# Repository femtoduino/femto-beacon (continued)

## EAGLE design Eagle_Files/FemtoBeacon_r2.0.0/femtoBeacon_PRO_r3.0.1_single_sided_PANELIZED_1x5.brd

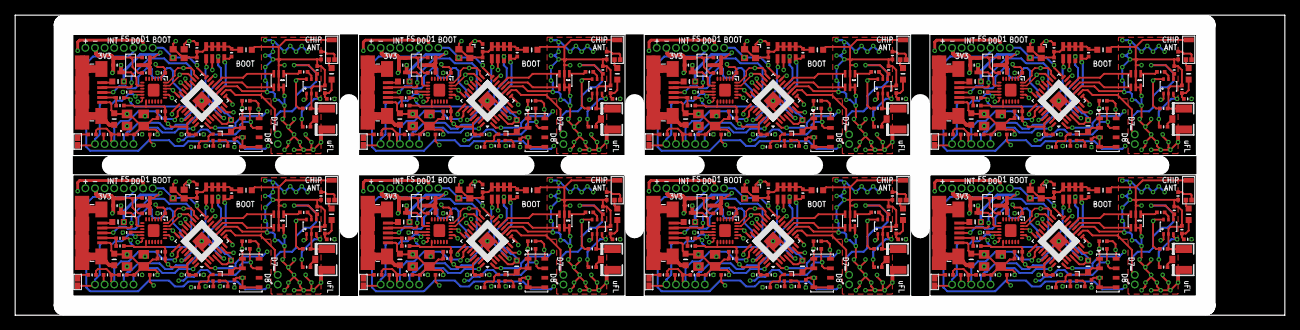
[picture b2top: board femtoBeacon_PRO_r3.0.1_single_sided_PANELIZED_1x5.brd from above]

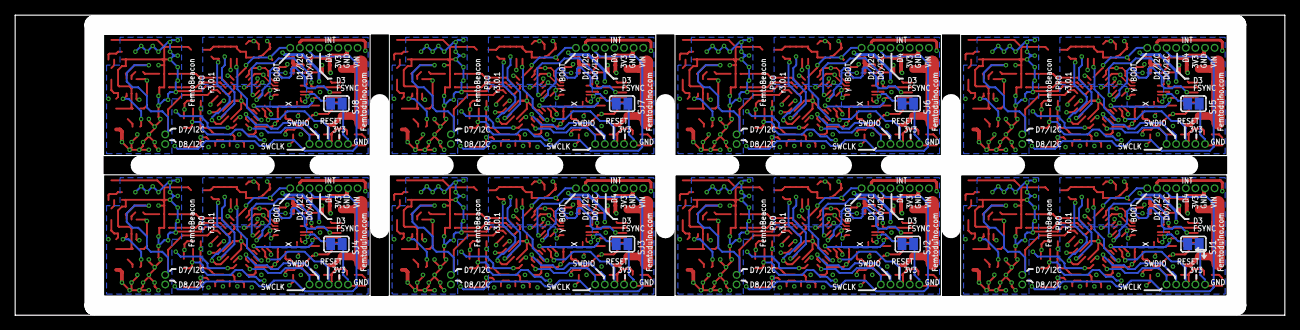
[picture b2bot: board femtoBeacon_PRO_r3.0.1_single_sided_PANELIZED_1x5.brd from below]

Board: 4 copper layers, 167.6 x 39.6 mm, 440 parts (8 on the bottom side), 352 nets.

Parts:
ASWITCH, ASWITCH1, ASWITCH2, ASWITCH3, ASWITCH4, ASWITCH5, ASWITCH6, ASWITCH7: AS222-92LF
BALUN, BALUN1, BALUN2, BALUN3, BALUN4, BALUN5, BALUN6, BALUN7: JOHANSON_2450BM15A0015E; 0805_BALUN
BARO, BARO1, BARO2, BARO3, BARO4, BARO5, BARO6, BARO7: MS5611-01BA03
BTN_RESET, BTN_RESET1, BTN_RESET2, BTN_RESET3, BTN_RESET4, BTN_RESET5, BTN_RESET6, BTN_RESET7: DNP; SPST_SMD
C1, C10, C16, C18, C24, C25, C28, C29, C30, C32, C39, C40, C47, C51, C52, C55, C62, C63, C70, C74, C75, C78, C85, C86, C93, C97, C98, C101, C108, C109, C116, C120, C121, C124, C131, C132, C139, C143, C144, C147, C154, C155, C162, C166, C167, C170, C177, C178: 0.1uF; _0402MP
C2, C8, C9, C11, C12, C41, C42, C43, C44, C45, C64, C65, C66, C67, C68, C87, C88, C89, C90, C91, C110, C111, C112, C113, C114, C133, C134, C135, C136, C137, C156, C157, C158, C159, C160, C179, C180, C181, C182, C183: 22pF, C0G, 5%; _0402MP
C3, C4, C33, C34, C56, C57, C79, C80, C102, C103, C125, C126, C148, C149, C171, C172: 10pF; _0402MP
C5, C6, C19, C20, C48, C49, C71, C72, C94, C95, C117, C118, C140, C141, C163, C164: 2.2uF; _0402MP
C7, C23, C50, C73, C96, C119, C142, C165: 0.47uF; _0402MP
C13, C35, C58, C81, C104, C127, C150, C173: DNP; _0402MP
C14, C15, C36, C37, C59, C60, C82, C83, C105, C106, C128, C129, C151, C152, C174, C175: 9pF; _0402MP
C17, C46, C69, C92, C115, C138, C161, C184: 1.2pF; _0402MP
C21, C22, C26, C27, C53, C54, C76, C77, C99, C100, C122, C123, C145, C146, C168, C169: 10uF; _0402MP
C31, C38, C61, C84, C107, C130, C153, C176: 10000pF; _0402MP
C_ARR, C_ARR1, C_ARR2, C_ARR3, C_ARR4, C_ARR5, C_ARR6, C_ARR7: 0.1uF; CAPACITOR_ARRAY_1206_MONO_1X4
FB1, FB2, FB3, FB4, FB5, FB6, FB7, FB8, FB9, FB10, FB11, FB12, FB13, FB14, FB15, FB16, FB17, FB18, FB19, FB20, FB21, FB22, FB23, FB24: _0603MP
IC, IC1, IC2, IC3, IC4, IC5, IC6, IC7: ATSAMR21E18A-MUT; QFN32
IMU, IMU1, IMU2, IMU3, IMU4, IMU5, IMU6, IMU7: MPU-9250; QFN_3X3MM
L1, L3, L5, L8, L10, L12, L14, L16: 1.8nH; _0603MP
L2, L4, L6, L7, L9, L11, L13, L15: 10uH; _0603MP
LDO_VREG, LDO_VREG1, LDO_VREG2, LDO_VREG3, LDO_VREG4, LDO_VREG5, LDO_VREG6, LDO_VREG7: MCP1700T-3302E/TT
R1, R3, R4, R6, R7, R10, R12, R15, R17, R18, R19, R21, R24, R26, R27, R28, R30, R33, R35, R36, R37, R39, R42, R44, R45, R46, R48, R51, R53, R54, R55, R57, R60, R62, R63, R64, R66, R69, R71, R72: 330; _0402MP
R2, R11, R20, R29, R38, R47, R56, R65: 10K; _0402MP
R5, R16, R25, R34, R43, R52, R61, R70: 100K; _0402MP
R8, R9, R13, R14, R22, R23, R31, R32, R40, R41, R49, R50, R58, R59, R67, R68: 2.2K; _0402MP
RGBLED, RGBLED1, RGBLED2, RGBLED3, RGBLED4, RGBLED5, RGBLED6, RGBLED7: LRTB_R48G
SJ1, SJ2, SJ3, SJ4, SJ5, SJ6, SJ7, SJ8: SOLDERJUMPER_CLOSEDWIRE
SMDANT, SMDANT1, SMDANT2, SMDANT3, SMDANT4, SMDANT5, SMDANT6, SMDANT7: PULSE_ANT_2.4GHZ; ANT_BAR
U$1, U$4, U$5, U$8, U$13, U$16, U$19, U$22: 1X8_ROUND
U$2, U$6, U$10, U$11, U$14, U$17, U$20, U$23: 1X5_ROUND
U$3, U$7, U$9, U$12, U$15, U$18, U$21, U$24: 1X2_ROUND
UFLANT, UFLANT1, UFLANT2, UFLANT3, UFLANT4, UFLANT5, UFLANT6, UFLANT7: U.FL
USB, USB1, USB2, USB3, USB4, USB5, USB6, USB7: USB_MICROB; USB_MICROB_PACKAGE
XTAL_BOARD, XTAL_BOARD1, XTAL_BOARD2, XTAL_BOARD3, XTAL_BOARD4, XTAL_BOARD5, XTAL_BOARD6, XTAL_BOARD7: 32MHz; FA-128
XTAL_RF, XTAL_RF1, XTAL_RF2, XTAL_RF3, XTAL_RF4, XTAL_RF5, XTAL_RF6, XTAL_RF7: 16MHz; TSX-3225

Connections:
3.3V: BARO.1, BARO.2, C5.1, C10.1, C16.1, C21.2, C29.1, C30.2, C31.2, IC.24, IC.30, IMU.P$1, IMU.P$8, IMU.P$13, IMU.P$22, L6.1, LDO_VREG.VOUT, R2.1, R5.2, R8.2, R9.2, RGBLED.1, U$5.P$3, U$10.P$2
3.3V1: BARO1.1, BARO1.2, C19.1, C24.1, C25.1, C26.2, C28.1, C38.2, C39.2, IC1.24, IC1.30, IMU1.P$1, IMU1.P$8, IMU1.P$13, IMU1.P$22, L2.1, LDO_VREG1.VOUT, R11.1, R13.2, R14.2, R16.2, RGBLED1.1, U$1.P$3, U$2.P$2
3.3V2: BARO2.1, BARO2.2, C48.1, C51.1, C52.1, C53.2, C55.1, C61.2, C62.2, IC2.24, IC2.30, IMU2.P$1, IMU2.P$8, IMU2.P$13, IMU2.P$22, L4.1, LDO_VREG2.VOUT, R20.1, R22.2, R23.2, R25.2, RGBLED2.1, U$4.P$3, U$6.P$2
3.3V3: BARO3.1, BARO3.2, C71.1, C74.1, C75.1, C76.2, C78.1, C84.2, C85.2, IC3.24, IC3.30, IMU3.P$1, IMU3.P$8, IMU3.P$13, IMU3.P$22, L7.1, LDO_VREG3.VOUT, R29.1, R31.2, R32.2, R34.2, RGBLED3.1, U$8.P$3, U$11.P$2
3.3V4: BARO4.1, BARO4.2, C94.1, C97.1, C98.1, C99.2, C101.1, C107.2, C108.2, IC4.24, IC4.30, IMU4.P$1, IMU4.P$8, IMU4.P$13, IMU4.P$22, L9.1, LDO_VREG4.VOUT, R38.1, R40.2, R41.2, R43.2, RGBLED4.1, U$13.P$3, U$14.P$2
3.3V5: BARO5.1, BARO5.2, C117.1, C120.1, C121.1, C122.2, C124.1, C130.2, C131.2, IC5.24, IC5.30, IMU5.P$1, IMU5.P$8, IMU5.P$13, IMU5.P$22, L11.1, LDO_VREG5.VOUT, R47.1, R49.2, R50.2, R52.2, RGBLED5.1, U$16.P$3, U$17.P$2
3.3V6: BARO6.1, BARO6.2, C140.1, C143.1, C144.1, C145.2, C147.1, C153.2, C154.2, IC6.24, IC6.30, IMU6.P$1, IMU6.P$8, IMU6.P$13, IMU6.P$22, L13.1, LDO_VREG6.VOUT, R56.1, R58.2, R59.2, R61.2, RGBLED6.1, U$19.P$3, U$20.P$2
3.3V7: BARO7.1, BARO7.2, C163.1, C166.1, C167.1, C168.2, C170.1, C176.2, C177.2, IC7.24, IC7.30, IMU7.P$1, IMU7.P$8, IMU7.P$13, IMU7.P$22, L15.1, LDO_VREG7.VOUT, R65.1, R67.2, R68.2, R70.2, RGBLED7.1, U$22.P$3, U$23.P$2
ANT_OUT: BALUN.1, C2.1
ANT_OUT1: BALUN1.1, C41.1
ANT_OUT2: BALUN2.1, C64.1
ANT_OUT3: BALUN3.1, C87.1
ANT_OUT4: BALUN4.1, C110.1
ANT_OUT5: BALUN5.1, C133.1
ANT_OUT6: BALUN6.1, C156.1
ANT_OUT7: BALUN7.1, C179.1
ANT_SMD: C12.2, C17.1, L1.1
ANT_SMD1: C45.2, C46.1, L3.1
ANT_SMD2: C68.2, C69.1, L5.1
ANT_SMD3: C91.2, C92.1, L8.1
ANT_SMD4: C114.2, C115.1, L10.1
ANT_SMD5: C137.2, C138.1, L12.1
ANT_SMD6: C160.2, C161.1, L14.1
ANT_SMD7: C183.2, C184.1, L16.1
ANT_UFL: C11.2, UFLANT.3
ANT_UFL1: C44.2, UFLANT1.3
ANT_UFL2: C67.2, UFLANT2.3
ANT_UFL3: C90.2, UFLANT3.3
ANT_UFL4: C113.2, UFLANT4.3
ANT_UFL5: C136.2, UFLANT5.3
ANT_UFL6: C159.2, UFLANT6.3
ANT_UFL7: C182.2, UFLANT7.3
AVDD: C_ARR.3, IC.5
AVDD1: C_ARR1.3, IC1.5
AVDD2: C_ARR2.3, IC2.5
AVDD3: C_ARR3.3, IC3.5
AVDD4: C_ARR4.3, IC4.5
AVDD5: C_ARR5.3, IC5.5
AVDD6: C_ARR6.3, IC6.5
AVDD7: C_ARR7.3, IC7.5
DVDD: C_ARR.5, IC.21
DVDD1: C_ARR1.5, IC1.21
DVDD2: C_ARR2.5, IC2.21
DVDD3: C_ARR3.5, IC3.21
DVDD4: C_ARR4.5, IC4.21
DVDD5: C_ARR5.5, IC5.21
DVDD6: C_ARR6.5, IC6.21
DVDD7: C_ARR7.5, IC7.21
GND: ASWITCH.PIN2, BALUN.2, BALUN.5, BALUN.6, BARO.3, BARO.4, BARO.5, BTN_RESET.2, C1.2, C3.1, C4.2, C5.2, C6.2, C7.2, C8.2, C9.2, C10.2, C13.2, C14.1, C15.2, C16.2, C17.2, C21.1, C22.1, C29.2, C30.1, C31.1, C32.2, C_ARR.2, C_ARR.4, C_ARR.6, C_ARR.8, FB1.2, FB3.1, FB3.2, IC.3, IC.6, IC.11, IC.14, IC.28, IC.33, IMU.P$20, LDO_VREG.GND, SJ1.1, SMDANT.3, U$5.P$2, U$10.P$1, UFLANT.1, UFLANT.2, USB.5, XTAL_BOARD.2, XTAL_BOARD.4, XTAL_RF.2, XTAL_RF.4
GND1: ASWITCH1.PIN2, BALUN1.2, BALUN1.5, BALUN1.6, BARO1.3, BARO1.4, BARO1.5, BTN_RESET1.2, C18.2, C19.2, C20.2, C23.2, C24.2, C25.2, C26.1, C27.1, C28.2, C33.1, C34.2, C35.2, C36.1, C37.2, C38.1, C39.1, C40.2, C42.2, C43.2, C46.2, C_ARR1.2, C_ARR1.4, C_ARR1.6, C_ARR1.8, FB4.2, FB6.1, FB6.2, IC1.3, IC1.6, IC1.11, IC1.14, IC1.28, IC1.33, IMU1.P$20, LDO_VREG1.GND, SJ2.1, SMDANT1.3, U$1.P$2, U$2.P$1, UFLANT1.1, UFLANT1.2, USB1.5, XTAL_BOARD1.2, XTAL_BOARD1.4, XTAL_RF1.2, XTAL_RF1.4
GND2: ASWITCH2.PIN2, BALUN2.2, BALUN2.5, BALUN2.6, BARO2.3, BARO2.4, BARO2.5, BTN_RESET2.2, C47.2, C48.2, C49.2, C50.2, C51.2, C52.2, C53.1, C54.1, C55.2, C56.1, C57.2, C58.2, C59.1, C60.2, C61.1, C62.1, C63.2, C65.2, C66.2, C69.2, C_ARR2.2, C_ARR2.4, C_ARR2.6, C_ARR2.8, FB7.2, FB9.1, FB9.2, IC2.3, IC2.6, IC2.11, IC2.14, IC2.28, IC2.33, IMU2.P$20, LDO_VREG2.GND, SJ3.1, SMDANT2.3, U$4.P$2, U$6.P$1, UFLANT2.1, UFLANT2.2, USB2.5, XTAL_BOARD2.2, XTAL_BOARD2.4, XTAL_RF2.2, XTAL_RF2.4
GND3: ASWITCH3.PIN2, BALUN3.2, BALUN3.5, BALUN3.6, BARO3.3, BARO3.4, BARO3.5, BTN_RESET3.2, C70.2, C71.2, C72.2, C73.2, C74.2, C75.2, C76.1, C77.1, C78.2, C79.1, C80.2, C81.2, C82.1, C83.2, C84.1, C85.1, C86.2, C88.2, C89.2, C92.2, C_ARR3.2, C_ARR3.4, C_ARR3.6, C_ARR3.8, FB10.2, FB12.1, FB12.2, IC3.3, IC3.6, IC3.11, IC3.14, IC3.28, IC3.33, IMU3.P$20, LDO_VREG3.GND, SJ4.1, SMDANT3.3, U$8.P$2, U$11.P$1, UFLANT3.1, UFLANT3.2, USB3.5, XTAL_BOARD3.2, XTAL_BOARD3.4, XTAL_RF3.2, XTAL_RF3.4
GND4: ASWITCH4.PIN2, BALUN4.2, BALUN4.5, BALUN4.6, BARO4.3, BARO4.4, BARO4.5, BTN_RESET4.2, C93.2, C94.2, C95.2, C96.2, C97.2, C98.2, C99.1, C100.1, C101.2, C102.1, C103.2, C104.2, C105.1, C106.2, C107.1, C108.1, C109.2, C111.2, C112.2, C115.2, C_ARR4.2, C_ARR4.4, C_ARR4.6, C_ARR4.8, FB13.2, FB15.1, FB15.2, IC4.3, IC4.6, IC4.11, IC4.14, IC4.28, IC4.33, IMU4.P$20, LDO_VREG4.GND, SJ5.1, SMDANT4.3, U$13.P$2, U$14.P$1, UFLANT4.1, UFLANT4.2, USB4.5, XTAL_BOARD4.2, XTAL_BOARD4.4, XTAL_RF4.2, XTAL_RF4.4
GND5: ASWITCH5.PIN2, BALUN5.2, BALUN5.5, BALUN5.6, BARO5.3, BARO5.4, BARO5.5, BTN_RESET5.2, C116.2, C117.2, C118.2, C119.2, C120.2, C121.2, C122.1, C123.1, C124.2, C125.1, C126.2, C127.2, C128.1, C129.2, C130.1, C131.1, C132.2, C134.2, C135.2, C138.2, C_ARR5.2, C_ARR5.4, C_ARR5.6, C_ARR5.8, FB16.2, FB18.1, FB18.2, IC5.3, IC5.6, IC5.11, IC5.14, IC5.28, IC5.33, IMU5.P$20, LDO_VREG5.GND, SJ6.1, SMDANT5.3, U$16.P$2, U$17.P$1, UFLANT5.1, UFLANT5.2, USB5.5, XTAL_BOARD5.2, XTAL_BOARD5.4, XTAL_RF5.2, XTAL_RF5.4
GND6: ASWITCH6.PIN2, BALUN6.2, BALUN6.5, BALUN6.6, BARO6.3, BARO6.4, BARO6.5, BTN_RESET6.2, C139.2, C140.2, C141.2, C142.2, C143.2, C144.2, C145.1, C146.1, C147.2, C148.1, C149.2, C150.2, C151.1, C152.2, C153.1, C154.1, C155.2, C157.2, C158.2, C161.2, C_ARR6.2, C_ARR6.4, C_ARR6.6, C_ARR6.8, FB19.2, FB21.1, FB21.2, IC6.3, IC6.6, IC6.11, IC6.14, IC6.28, IC6.33, IMU6.P$20, LDO_VREG6.GND, SJ7.1, SMDANT6.3, U$19.P$2, U$20.P$1, UFLANT6.1, UFLANT6.2, USB6.5, XTAL_BOARD6.2, XTAL_BOARD6.4, XTAL_RF6.2, XTAL_RF6.4
GND7: ASWITCH7.PIN2, BALUN7.2, BALUN7.5, BALUN7.6, BARO7.3, BARO7.4, BARO7.5, BTN_RESET7.2, C162.2, C163.2, C164.2, C165.2, C166.2, C167.2, C168.1, C169.1, C170.2, C171.1, C172.2, C173.2, C174.1, C175.2, C176.1, C177.1, C178.2, C180.2, C181.2, C184.2, C_ARR7.2, C_ARR7.4, C_ARR7.6, C_ARR7.8, FB22.2, FB24.1, FB24.2, IC7.3, IC7.6, IC7.11, IC7.14, IC7.28, IC7.33, IMU7.P$20, LDO_VREG7.GND, SJ8.1, SMDANT7.3, U$22.P$2, U$23.P$1, UFLANT7.1, UFLANT7.2, USB7.5, XTAL_BOARD7.2, XTAL_BOARD7.4, XTAL_RF7.2, XTAL_RF7.4
unnamed: L1.2, SMDANT.1
unnamed: C13.1, SMDANT.2
unnamed: ASWITCH.PIN5, C2.2
unnamed: C32.1, IMU.P$10
unnamed: FB1.1, USB.6, USB.7, USB.8, USB.9, USB.10, USB.11
unnamed: R3.1, R5.1, USB.4
unnamed: FB2.1, USB.1
unnamed: R6.2, RGBLED.3
unnamed: R7.2, RGBLED.4
unnamed: ASWITCH.PIN3, C11.1
unnamed: ASWITCH.PIN1, C12.1
unnamed: BTN_RESET1.1, R10.1
unnamed: R4.2, RGBLED.2
unnamed: R12.2, RGBLED1.2
unnamed: C35.1, SMDANT1.2
unnamed: C40.1, IMU1.P$10
unnamed: FB4.1, USB1.6, USB1.7, USB1.8, USB1.9, USB1.10, USB1.11
unnamed: R15.1, R16.1, USB1.4
unnamed: R17.2, RGBLED1.3
unnamed: R18.2, RGBLED1.4
unnamed: FB5.1, USB1.1
unnamed: ASWITCH1.PIN3, C44.1
unnamed: ASWITCH1.PIN1, C45.1
unnamed: ASWITCH1.PIN5, C41.2
unnamed: L3.2, SMDANT1.1
unnamed: BTN_RESET.1, R1.1
unnamed: BTN_RESET2.1, R19.1
unnamed: R21.2, RGBLED2.2
unnamed: C58.1, SMDANT2.2
unnamed: C63.1, IMU2.P$10
unnamed: FB7.1, USB2.6, USB2.7, USB2.8, USB2.9, USB2.10, USB2.11
unnamed: R24.1, R25.1, USB2.4
unnamed: R26.2, RGBLED2.3
unnamed: R27.2, RGBLED2.4
unnamed: FB8.1, USB2.1
unnamed: ASWITCH2.PIN3, C67.1
unnamed: ASWITCH2.PIN1, C68.1
unnamed: ASWITCH2.PIN5, C64.2
unnamed: L5.2, SMDANT2.1
unnamed: BTN_RESET3.1, R28.1
unnamed: R30.2, RGBLED3.2
unnamed: C81.1, SMDANT3.2
unnamed: C86.1, IMU3.P$10
unnamed: FB10.1, USB3.6, USB3.7, USB3.8, USB3.9, USB3.10, USB3.11
unnamed: R33.1, R34.1, USB3.4
unnamed: R35.2, RGBLED3.3
unnamed: R36.2, RGBLED3.4
unnamed: FB11.1, USB3.1
unnamed: ASWITCH3.PIN3, C90.1
unnamed: ASWITCH3.PIN1, C91.1
unnamed: ASWITCH3.PIN5, C87.2
unnamed: L8.2, SMDANT3.1
unnamed: BTN_RESET4.1, R37.1
unnamed: R39.2, RGBLED4.2
unnamed: C104.1, SMDANT4.2
unnamed: C109.1, IMU4.P$10
unnamed: FB13.1, USB4.6, USB4.7, USB4.8, USB4.9, USB4.10, USB4.11
unnamed: R42.1, R43.1, USB4.4
unnamed: R44.2, RGBLED4.3
unnamed: R45.2, RGBLED4.4
unnamed: FB14.1, USB4.1
unnamed: ASWITCH4.PIN3, C113.1
unnamed: ASWITCH4.PIN1, C114.1
unnamed: ASWITCH4.PIN5, C110.2
unnamed: L10.2, SMDANT4.1
unnamed: BTN_RESET5.1, R46.1
unnamed: R48.2, RGBLED5.2
unnamed: C127.1, SMDANT5.2
unnamed: C132.1, IMU5.P$10
unnamed: FB16.1, USB5.6, USB5.7, USB5.8, USB5.9, USB5.10, USB5.11
unnamed: R51.1, R52.1, USB5.4
unnamed: R53.2, RGBLED5.3
unnamed: R54.2, RGBLED5.4
unnamed: FB17.1, USB5.1
unnamed: ASWITCH5.PIN3, C136.1
unnamed: ASWITCH5.PIN1, C137.1
unnamed: ASWITCH5.PIN5, C133.2
unnamed: L12.2, SMDANT5.1
unnamed: BTN_RESET6.1, R55.1
unnamed: R57.2, RGBLED6.2
unnamed: C150.1, SMDANT6.2
unnamed: C155.1, IMU6.P$10
unnamed: FB19.1, USB6.6, USB6.7, USB6.8, USB6.9, USB6.10, USB6.11
unnamed: R60.1, R61.1, USB6.4
unnamed: R62.2, RGBLED6.3
unnamed: R63.2, RGBLED6.4
unnamed: FB20.1, USB6.1
unnamed: ASWITCH6.PIN3, C159.1
unnamed: ASWITCH6.PIN1, C160.1
unnamed: ASWITCH6.PIN5, C156.2
unnamed: L14.2, SMDANT6.1
unnamed: BTN_RESET7.1, R64.1
unnamed: R66.2, RGBLED7.2
unnamed: C173.1, SMDANT7.2
unnamed: C178.1, IMU7.P$10
unnamed: FB22.1, USB7.6, USB7.7, USB7.8, USB7.9, USB7.10, USB7.11
unnamed: R69.1, R70.1, USB7.4
unnamed: R71.2, RGBLED7.3
unnamed: R72.2, RGBLED7.4
unnamed: FB23.1, USB7.1
unnamed: ASWITCH7.PIN3, C182.1
unnamed: ASWITCH7.PIN1, C183.1
unnamed: ASWITCH7.PIN5, C179.2
unnamed: L16.2, SMDANT7.1
PA1: IC1.27, R15.2
PA2: IC2.27, R24.2
PA3: IC3.27, R33.2
PA4: IC4.27, R42.2
PA5: IC5.27, R51.2
PA6: IC6.27, R60.2
PA06(R): IC.7, R4.1
PA06(R)1: IC1.7, R12.1
PA06(R)2: IC2.7, R21.1
PA06(R)3: IC3.7, R30.1
PA06(R)4: IC4.7, R39.1
PA06(R)5: IC5.7, R48.1
PA06(R)6: IC6.7, R57.1
PA06(R)7: IC7.7, R66.1
PA7: IC7.27, R69.2
PA07(G): IC.8, R6.1
PA07(G)1: IC1.8, R17.1
PA07(G)2: IC2.8, R26.1
PA07(G)3: IC3.8, R35.1
PA07(G)4: IC4.8, R44.1
PA07(G)5: IC5.8, R53.1
PA07(G)6: IC6.8, R62.1
PA07(G)7: IC7.8, R71.1
PA08/I2C: ASWITCH.PIN6, C9.1, IC.9, U$9.P$2
PA08/I2C1: ASWITCH1.PIN6, C43.1, IC1.9, U$3.P$2
PA08/I2C2: ASWITCH2.PIN6, C66.1, IC2.9, U$7.P$2
PA08/I2C3: ASWITCH3.PIN6, C89.1, IC3.9, U$12.P$2
PA08/I2C4: ASWITCH4.PIN6, C112.1, IC4.9, U$15.P$2
PA08/I2C5: ASWITCH5.PIN6, C135.1, IC5.9, U$18.P$2
PA08/I2C6: ASWITCH6.PIN6, C158.1, IC6.9, U$21.P$2
PA08/I2C7: ASWITCH7.PIN6, C181.1, IC7.9, U$24.P$2
PA09/I2C: ASWITCH.PIN4, C8.1, IC.10, U$9.P$1
PA09/I2C1: ASWITCH1.PIN4, C42.1, IC1.10, U$3.P$1
PA09/I2C2: ASWITCH2.PIN4, C65.1, IC2.10, U$7.P$1
PA09/I2C3: ASWITCH3.PIN4, C88.1, IC3.10, U$12.P$1
PA09/I2C4: ASWITCH4.PIN4, C111.1, IC4.10, U$15.P$1
PA09/I2C5: ASWITCH5.PIN4, C134.1, IC5.10, U$18.P$1
PA09/I2C6: ASWITCH6.PIN4, C157.1, IC6.10, U$21.P$1
PA09/I2C7: ASWITCH7.PIN4, C180.1, IC7.10, U$24.P$1
PA14/XIN_MC: C3.2, IC.15, XTAL_BOARD.1
PA14/XIN_MC1: C33.2, IC1.15, XTAL_BOARD1.1
PA14/XIN_MC2: C56.2, IC2.15, XTAL_BOARD2.1
PA14/XIN_MC3: C79.2, IC3.15, XTAL_BOARD3.1
PA14/XIN_MC4: C102.2, IC4.15, XTAL_BOARD4.1
PA14/XIN_MC5: C125.2, IC5.15, XTAL_BOARD5.1
PA14/XIN_MC6: C148.2, IC6.15, XTAL_BOARD6.1
PA14/XIN_MC7: C171.2, IC7.15, XTAL_BOARD7.1
PA15/XOUT_MC: C4.1, IC.16, U$5.P$8, XTAL_BOARD.3
PA15/XOUT_MC1: C34.1, IC1.16, U$1.P$8, XTAL_BOARD1.3
PA15/XOUT_MC2: C57.1, IC2.16, U$4.P$8, XTAL_BOARD2.3
PA15/XOUT_MC3: C80.1, IC3.16, U$8.P$8, XTAL_BOARD3.3
PA15/XOUT_MC4: C103.1, IC4.16, U$13.P$8, XTAL_BOARD4.3
PA15/XOUT_MC5: C126.1, IC5.16, U$16.P$8, XTAL_BOARD5.3
PA15/XOUT_MC6: C149.1, IC6.16, U$19.P$8, XTAL_BOARD6.3
PA15/XOUT_MC7: C172.1, IC7.16, U$22.P$8, XTAL_BOARD7.3
PA16/I2C: BARO.7, IC.17, IMU.P$24, R8.1, U$5.P$7
PA16/I2C1: BARO1.7, IC1.17, IMU1.P$24, R13.1, U$1.P$7
PA16/I2C2: BARO2.7, IC2.17, IMU2.P$24, R22.1, U$4.P$7
PA16/I2C3: BARO3.7, IC3.17, IMU3.P$24, R31.1, U$8.P$7
PA16/I2C4: BARO4.7, IC4.17, IMU4.P$24, R40.1, U$13.P$7
PA16/I2C5: BARO5.7, IC5.17, IMU5.P$24, R49.1, U$16.P$7
PA16/I2C6: BARO6.7, IC6.17, IMU6.P$24, R58.1, U$19.P$7
PA16/I2C7: BARO7.7, IC7.17, IMU7.P$24, R67.1, U$22.P$7
PA17/I2C: BARO.8, IC.18, IMU.P$23, R9.1, U$5.P$6
PA17/I2C1: BARO1.8, IC1.18, IMU1.P$23, R14.1, U$1.P$6
PA17/I2C2: BARO2.8, IC2.18, IMU2.P$23, R23.1, U$4.P$6
PA17/I2C3: BARO3.8, IC3.18, IMU3.P$23, R32.1, U$8.P$6
PA17/I2C4: BARO4.8, IC4.18, IMU4.P$23, R41.1, U$13.P$6
PA17/I2C5: BARO5.8, IC5.18, IMU5.P$23, R50.1, U$16.P$6
PA17/I2C6: BARO6.8, IC6.18, IMU6.P$23, R59.1, U$19.P$6
PA17/I2C7: BARO7.8, IC7.18, IMU7.P$23, R68.1, U$22.P$6
PA18/FSYNC: IC.19, IMU.P$11, SJ1.2, U$5.P$5
PA18/FSYNC1: IC1.19, IMU1.P$11, SJ2.2, U$1.P$5
PA18/FSYNC2: IC2.19, IMU2.P$11, SJ3.2, U$4.P$5
PA18/FSYNC3: IC3.19, IMU3.P$11, SJ4.2, U$8.P$5
PA18/FSYNC4: IC4.19, IMU4.P$11, SJ5.2, U$13.P$5
PA18/FSYNC5: IC5.19, IMU5.P$11, SJ6.2, U$16.P$5
PA18/FSYNC6: IC6.19, IMU6.P$11, SJ7.2, U$19.P$5
PA18/FSYNC7: IC7.19, IMU7.P$11, SJ8.2, U$22.P$5
PA19/INT: IC.20, IMU.P$12, U$5.P$4
PA19/INT1: IC1.20, IMU1.P$12, U$1.P$4
PA19/INT2: IC2.20, IMU2.P$12, U$4.P$4
PA19/INT3: IC3.20, IMU3.P$12, U$8.P$4
PA19/INT4: IC4.20, IMU4.P$12, U$13.P$4
PA19/INT5: IC5.20, IMU5.P$12, U$16.P$4
PA19/INT6: IC6.20, IMU6.P$12, U$19.P$4
PA19/INT7: IC7.20, IMU7.P$12, U$22.P$4
PA24/USBDM: IC.22, USB.2
PA24/USBDM1: IC1.22, USB1.2
PA24/USBDM2: IC2.22, USB2.2
PA24/USBDM3: IC3.22, USB3.2
PA24/USBDM4: IC4.22, USB4.2
PA24/USBDM5: IC5.22, USB5.2
PA24/USBDM6: IC6.22, USB6.2
PA24/USBDM7: IC7.22, USB7.2
PA25/USBDP: IC.23, USB.3
PA25/USBDP1: IC1.23, USB1.3
PA25/USBDP2: IC2.23, USB2.3
PA25/USBDP3: IC3.23, USB3.3
PA25/USBDP4: IC4.23, USB4.3
PA25/USBDP5: IC5.23, USB5.3
PA25/USBDP6: IC6.23, USB6.3
PA25/USBDP7: IC7.23, USB7.3
PA27(B): IC.25, R7.1
PA27(B)1: IC1.25, R18.1
PA27(B)2: IC2.25, R27.1
PA27(B)3: IC3.25, R36.1
PA27(B)4: IC4.25, R45.1
PA27(B)5: IC5.25, R54.1
PA27(B)6: IC6.25, R63.1
PA27(B)7: IC7.25, R72.1
PA28: IC.27, R3.2
PA30/SWCLK: IC.31, U$10.P$4
PA30/SWCLK1: IC1.31, U$2.P$4
PA30/SWCLK2: IC2.31, U$6.P$4
PA30/SWCLK3: IC3.31, U$11.P$4
PA30/SWCLK4: IC4.31, U$14.P$4
PA30/SWCLK5: IC5.31, U$17.P$4
PA30/SWCLK6: IC6.31, U$20.P$4
PA30/SWCLK7: IC7.31, U$23.P$4
PA31/SWDIO: IC.32, U$10.P$5
PA31/SWDIO1: IC1.32, U$2.P$5
PA31/SWDIO2: IC2.32, U$6.P$5
PA31/SWDIO3: IC3.32, U$11.P$5
PA31/SWDIO4: IC4.32, U$14.P$5
PA31/SWDIO5: IC5.32, U$17.P$5
PA31/SWDIO6: IC6.32, U$20.P$5
PA31/SWDIO7: IC7.32, U$23.P$5
RESET: C1.1, IC.26, R1.2, R2.2, U$10.P$3
RESET1: C18.1, IC1.26, R10.2, R11.2, U$2.P$3
RESET2: C47.1, IC2.26, R19.2, R20.2, U$6.P$3
RESET3: C70.1, IC3.26, R28.2, R29.2, U$11.P$3
RESET4: C93.1, IC4.26, R37.2, R38.2, U$14.P$3
RESET5: C116.1, IC5.26, R46.2, R47.2, U$17.P$3
RESET6: C139.1, IC6.26, R55.2, R56.2, U$20.P$3
RESET7: C162.1, IC7.26, R64.2, R65.2, U$23.P$3
RFN: BALUN.3, IC.13
RFN1: BALUN1.3, IC1.13
RFN2: BALUN2.3, IC2.13
RFN3: BALUN3.3, IC3.13
RFN4: BALUN4.3, IC4.13
RFN5: BALUN5.3, IC5.13
RFN6: BALUN6.3, IC6.13
RFN7: BALUN7.3, IC7.13
RFP: BALUN.4, IC.12
RFP1: BALUN1.4, IC1.12
RFP2: BALUN2.4, IC2.12
RFP3: BALUN3.4, IC3.12
RFP4: BALUN4.4, IC4.12
RFP5: BALUN5.4, IC5.12
RFP6: BALUN6.4, IC6.12
RFP7: BALUN7.4, IC7.12
VDDANA: C22.2, C_ARR.1, IC.4, L6.2
VDDANA1: C27.2, C_ARR1.1, IC1.4, L2.2
VDDANA2: C54.2, C_ARR2.1, IC2.4, L4.2
VDDANA3: C77.2, C_ARR3.1, IC3.4, L7.2
VDDANA4: C100.2, C_ARR4.1, IC4.4, L9.2
VDDANA5: C123.2, C_ARR5.1, IC5.4, L11.2
VDDANA6: C146.2, C_ARR6.1, IC6.4, L13.2
VDDANA7: C169.2, C_ARR7.1, IC7.4, L15.2
VDDCORE: C_ARR.7, IC.29
VDDCORE1: C_ARR1.7, IC1.29
VDDCORE2: C_ARR2.7, IC2.29
VDDCORE3: C_ARR3.7, IC3.29
VDDCORE4: C_ARR4.7, IC4.29
VDDCORE5: C_ARR5.7, IC5.29
VDDCORE6: C_ARR6.7, IC6.29
VDDCORE7: C_ARR7.7, IC7.29
VIN: C6.1, C7.1, FB2.2, LDO_VREG.VIN, U$5.P$1
VIN1: C20.1, C23.1, FB5.2, LDO_VREG1.VIN, U$1.P$1
VIN2: C49.1, C50.1, FB8.2, LDO_VREG2.VIN, U$4.P$1
VIN3: C72.1, C73.1, FB11.2, LDO_VREG3.VIN, U$8.P$1
VIN4: C95.1, C96.1, FB14.2, LDO_VREG4.VIN, U$13.P$1
VIN5: C118.1, C119.1, FB17.2, LDO_VREG5.VIN, U$16.P$1
VIN6: C141.1, C142.1, FB20.2, LDO_VREG6.VIN, U$19.P$1
VIN7: C164.1, C165.1, FB23.2, LDO_VREG7.VIN, U$22.P$1
XTALIN: C14.2, IC.2, XTAL_RF.1
XTALIN1: C36.2, IC1.2, XTAL_RF1.1
XTALIN2: C59.2, IC2.2, XTAL_RF2.1
XTALIN3: C82.2, IC3.2, XTAL_RF3.1
XTALIN4: C105.2, IC4.2, XTAL_RF4.1
XTALIN5: C128.2, IC5.2, XTAL_RF5.1
XTALIN6: C151.2, IC6.2, XTAL_RF6.1
XTALIN7: C174.2, IC7.2, XTAL_RF7.1
XTALOUT: C15.1, IC.1, XTAL_RF.3
XTALOUT1: C37.1, IC1.1, XTAL_RF1.3
XTALOUT2: C60.1, IC2.1, XTAL_RF2.3
XTALOUT3: C83.1, IC3.1, XTAL_RF3.3
XTALOUT4: C106.1, IC4.1, XTAL_RF4.3
XTALOUT5: C129.1, IC5.1, XTAL_RF5.3
XTALOUT6: C152.1, IC6.1, XTAL_RF6.3
XTALOUT7: C175.1, IC7.1, XTAL_RF7.3

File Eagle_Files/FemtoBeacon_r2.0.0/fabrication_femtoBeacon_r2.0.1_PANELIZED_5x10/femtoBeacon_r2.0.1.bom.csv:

"Qty","Value","Device","Package","Parts","Description","DIGIKEY_PART"
"1",,"FERRITE_0603MP","_0603MP","FB1","Ferrite Bead",
"10","0.1uF","CAPACITOR_0201","PART","C1, C2, C8, C9, C10, C16, C17, C29, C30, C32",,"490-3194-1-ND"
"1","0.47uF","CAPACITOR_0201","PART","C7",,
"1","10K","RESISTOR_0201","PART","R2",,
"1","10nF","CAPACITOR_0201","PART","C31",,"490-3194-1-ND"
"2","10pF","CAPACITOR_0201","PART","C3, C4",,"490-3194-1-ND"
"2","10uF","CAP_CERAMIC_0402MP","_0402MP","C21, C22","Ceramic Capacitors",
"1","10uH","INDUCTOR_0603MP","_0603MP","L6","Inductors",
"1","12MHz","TSX-3225","TSX-3225","XOSC",,
"1","16MHz","TSX-3225","TSX-3225","XOSCRF",,
"2","2.2K","RESISTOR_0201","PART","R8, R9",,
"2","2.2uF","CAP_CERAMIC_0402MP","_0402MP","C5, C6","Ceramic Capacitors",
"2","22pF, C0G, 5%","CAPACITOR_0201","PART","C11, C12",,"490-3194-1-ND"
"2","330","RESISTOR_0201","PART","R1, R4",,
"2","9pF","CAPACITOR_0201","PART","C14, C15",,"490-3194-1-ND"
"1","ATSAMR21E18A-MUT","ATSAMR21E18A-MUT","QFN32","IC","This is the ATMEL SAMR21E QFN-32. ATSAMR21E18A",
"1","BLUE","LED0603_NOOUTLINE","CHIPLED_0603_NOOUTLINE","LED2","LED",
"1","JOHANSON_2450BM15A0015E","JOHANSON_2450BM15A0015E","0805_BALUN","BAL",,
"1","MCP1700T-3302E/TT","MCP1700T-3302E/TT","MCP1700T-3302E/TT","LDO_VREG","Microchip LDO ""MCP1700"" in a 3-Pin SOT-23 package.",
"1","MPU-9250","MPU-9250","QFN_3X3MM","IMU",,
"1","MS5611-01BA03","MS5611-01BA03","MS5611-01BA03","BARO",,
"1","PULSE_ANT_2.4GHZ","PULSE_ANT_2.4GHZ","ANT_BAR","ANT1","Manufacturer part #W3008",
"1","USB_MICROB","USB_MICROB","USB_MICROB_PACKAGE","USB","This is the hirose ZX62-B-5PA(11) MICRO-USB B Type female connection.",

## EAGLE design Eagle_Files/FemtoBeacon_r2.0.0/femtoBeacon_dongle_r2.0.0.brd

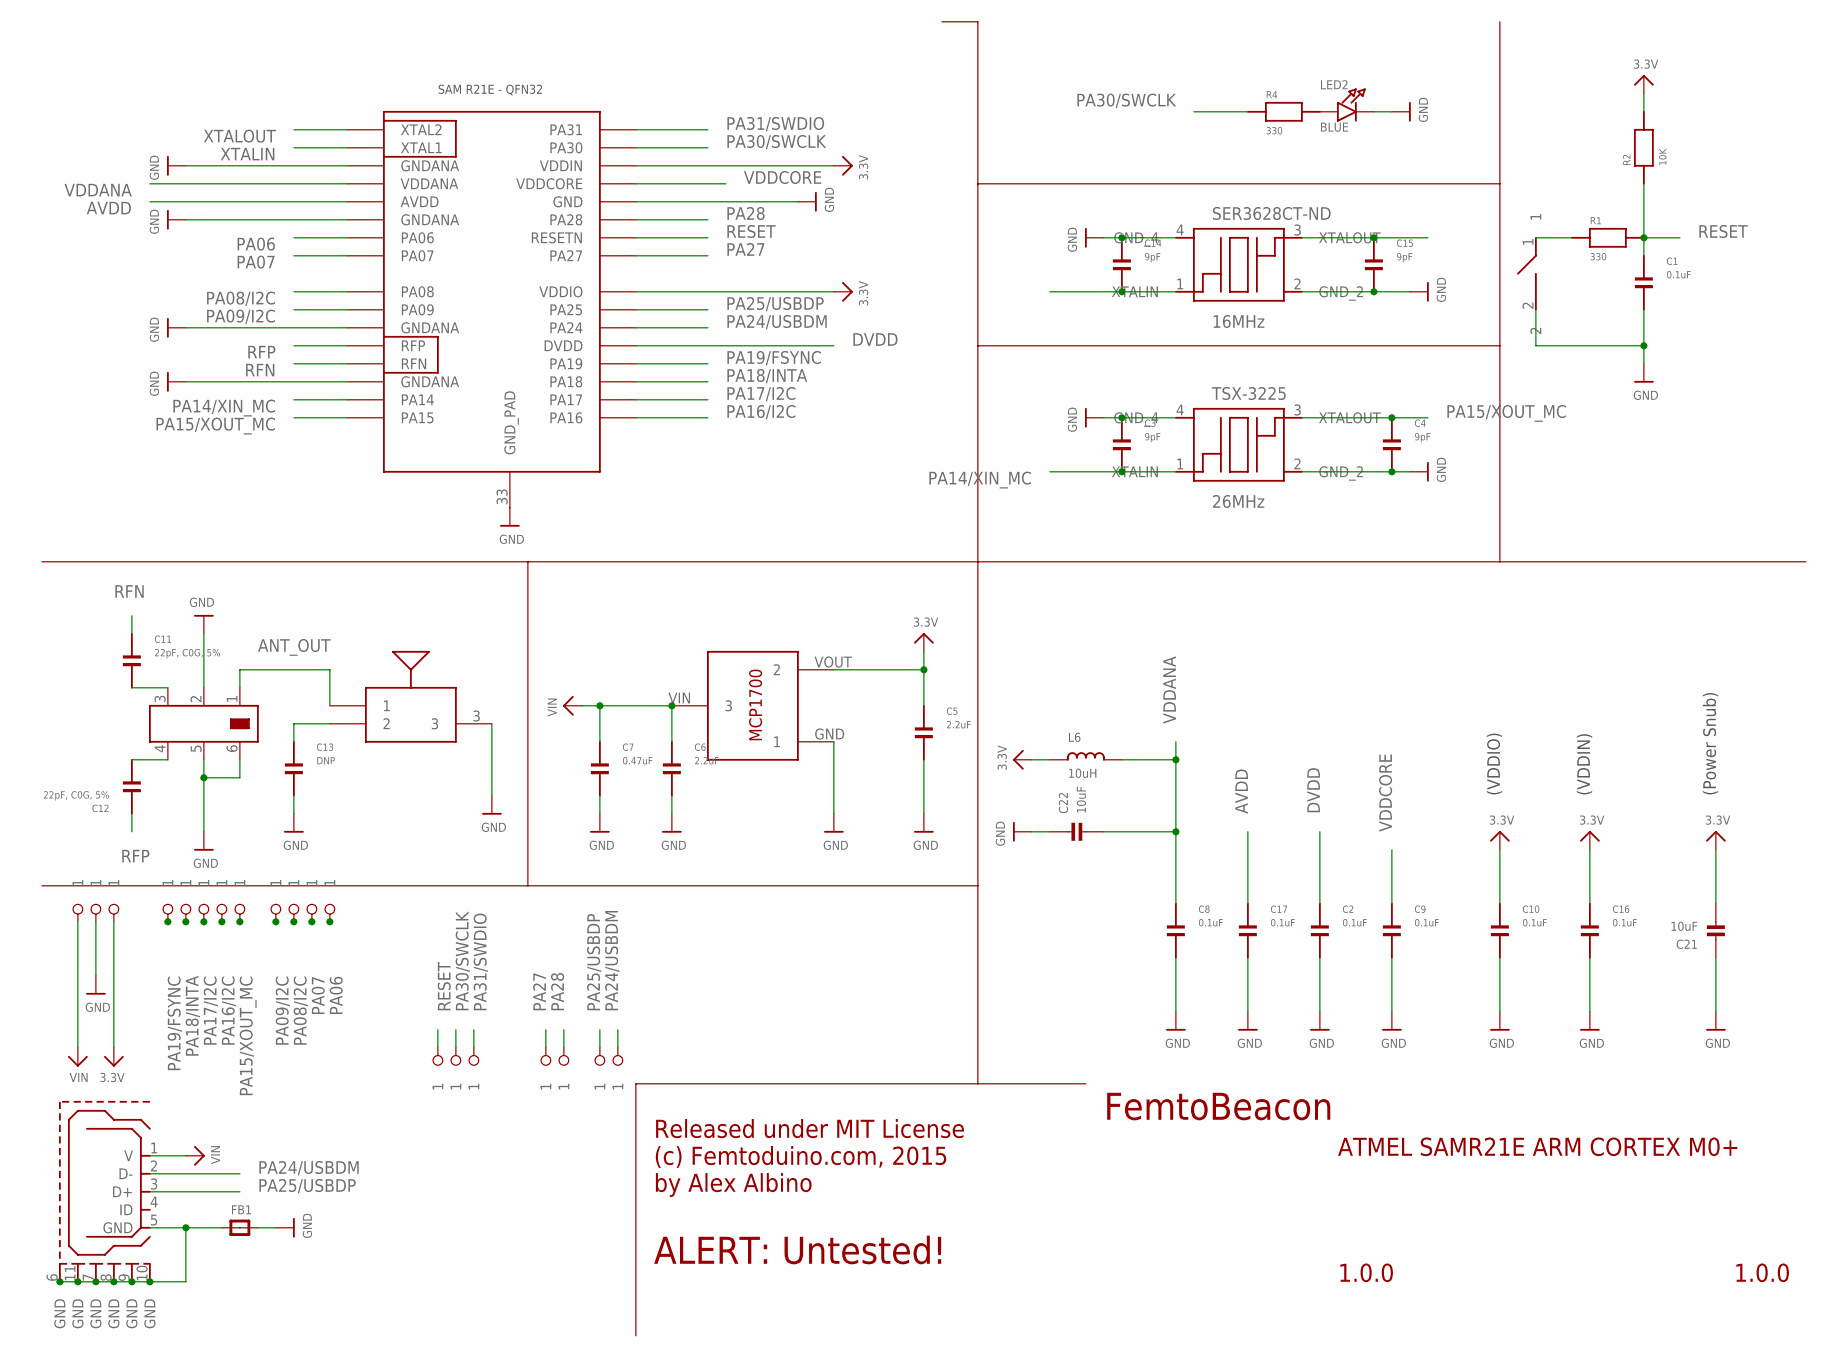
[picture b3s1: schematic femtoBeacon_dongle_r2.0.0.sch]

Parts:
ANT1: PULSE_ANT_2.4GHZ; ANT_BAR
BTN: DNP; SPST_SMD
C1, C8, C9, C10, C16, C17: 0.1uF; PART; DIGIKEY_PART 490-3194-1-ND
C2: 0.1uF; PART
C3, C4, C14, C15: 9pF; PART; DIGIKEY_PART 490-3194-1-ND
C5, C6: 2.2uF; PART
C7: 0.47uF; PART
C11, C12: 22pF, C0G, 5%; PART; DIGIKEY_PART 490-3194-1-ND
C13: DNP; PART; DIGIKEY_PART 490-3194-1-ND
C21, C22: 10uF; _0402MP
FB1: FERRITE_0603MP; _0603MP
L6: 10uH; _0603MP
LDO_VREG: MCP1700T-3302E/TT
LED2: BLUE; CHIPLED_0603_NOOUTLINE
R1, R4: 330; PART
R2: 10K; PART
SER3628CT-ND: 16MHz; TSX-3225
TSX-3225: 26MHz; TSX-3225
U$1, U$2, U$5, U$7, U$9, U$10, U$35, U$36, U$37, U$38, U$39, U$41, U$42, U$43, U$45, U$46, U$47, U$48, U$54: 1X1_ROUND
U$8: USB_MICROB; USB_MICROB_PACKAGE
U$12: JOHANSON_2450BM15A0015E; 0805_BALUN
U$76: ATSAMR21E18A-MUT; QFN32

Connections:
3.3V: C5.1, C10.1, C16.1, C21.2, L6.1, LDO_VREG.VOUT (2), R2.2, U$5.P$1, U$76.24 (VDDIO), U$76.30 (VDDIN)
ANT_OUT: ANT1.1, U$12.1
AVDD: C17.1, U$76.5 (AVDD)
DVDD: C2.1, U$76.21 (DVDD)
GND: ANT1.3, BTN.2, C1.2, C2.2, C3.1, C4.2, C5.2, C6.2, C7.2, C8.2, C9.2, C10.2, C13.2, C14.1, C15.2, C16.2, C17.2, C21.1, C22.1, FB1.2, LDO_VREG.GND (1), LED2.C, SER3628CT-ND.2 (GND_2), SER3628CT-ND.4 (GND_4), TSX-3225.2 (GND_2), TSX-3225.4 (GND_4), U$2.P$1, U$12.2, U$12.5, U$12.6, U$76.3 (GNDANA), U$76.6 (GNDANA), U$76.11 (GNDANA), U$76.14 (GNDANA), U$76.28 (GND), U$76.33 (GND_PAD)
unnamed: C11.2, U$12.3
unnamed: ANT1.2, C13.1
unnamed: C12.2, U$12.4
unnamed: FB1.1, U$8.5 (GND), U$8.6 (GND), U$8.7 (GND), U$8.8 (GND), U$8.9 (GND), U$8.10 (GND), U$8.11 (GND)
unnamed: LED2.A, R4.2
unnamed: BTN.1, R1.1
PA06: U$54.P$1, U$76.7 (PA06)
PA07: U$43.P$1, U$76.8 (PA07)
PA08/I2C: U$42.P$1, U$76.9 (PA08)
PA09/I2C: U$41.P$1, U$76.10 (PA09)
PA14/XIN_MC: C3.2, TSX-3225.1 (XTALIN), U$76.15 (PA14)
PA15/XOUT_MC: C4.1, TSX-3225.3 (XTALOUT), U$39.P$1, U$76.16 (PA15)
PA16/I2C: U$38.P$1, U$76.17 (PA16)
PA17/I2C: U$37.P$1, U$76.18 (PA17)
PA18/INTA: U$36.P$1, U$76.19 (PA18)
PA19/FSYNC: U$35.P$1, U$76.20 (PA19)
PA24/USBDM: U$8.2 (D-), U$9.P$1, U$76.22 (PA24)
PA25/USBDP: U$8.3 (D+), U$10.P$1, U$76.23 (PA25)
PA27: U$7.P$1, U$76.25 (PA27)
PA28: U$48.P$1, U$76.27 (PA28)
PA30/SWCLK: R4.1, U$46.P$1, U$76.31 (PA30)
PA31/SWDIO: U$47.P$1, U$76.32 (PA31)
RESET: C1.1, R1.2, R2.1, U$45.P$1, U$76.26 (RESETN)
RFN: C11.1, U$76.13 (RFN)
RFP: C12.1, U$76.12 (RFP)
VDDANA: C8.1, C22.2, L6.2, U$76.4 (VDDANA)
VDDCORE: C9.1, U$76.29 (VDDCORE)
VIN: C6.1, C7.1, LDO_VREG.VIN (3), U$1.P$1, U$8.1 (V)
XTALIN: C14.2, SER3628CT-ND.1 (XTALIN), U$76.2 (XTAL1)
XTALOUT: C15.1, SER3628CT-ND.3 (XTALOUT), U$76.1 (XTAL2)

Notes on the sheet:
FemtoBeacon
1.0.0
ATMEL SAMR21E ARM CORTEX M0+
Released under MIT License (c) Femtoduino.com, 2015 by Alex Albino
ALERT: Untested!
(Power Snub)
(VDDIO)
(VDDIN)

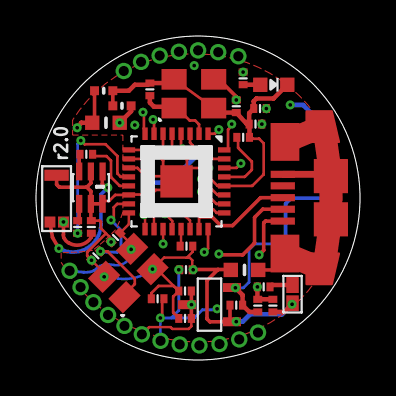
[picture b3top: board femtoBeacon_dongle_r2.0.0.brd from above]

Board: 4 copper layers, 18.0 x 18.0 mm, 52 parts (0 on the bottom side), 35 nets.
